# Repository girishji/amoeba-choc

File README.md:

# amoeba-choc
Single switch pcb for Kailh Choc keyboard switch (KiCad project).

If you are interested in using, here is some info:
- Use 1.2mm thickness pcb (suitable for Choc 1350 hotswap sockets)
- If you are using jlcpcb pick the option to let them panelize (5x5 will
    fit in 100x100 board ($2+shipping))
- Diodes are SOD-123 (1N4148)
- LED is SMD 6028 monochrome (you can get white ones from aliexpress). Wire
  them in a charlieplex and use IS31FL3731 LED driver (Adafruit sells a breakout
  board). 
- Some notes on LED:
    - IS31FL3731 drives (PWM) LEDs at 8k Hz. This causes audible buzz
      (annoying) from the ceramic capacitors on board of Adafruit board. To
      remove noise replace the 2 10uF capacitors with Tantalum capacitors.
      Also, you can create your own circuit for IS31FL3731 (jlcpcb stocks the
      parts) using the datasheet from Lumissil. Adafruit also has Eagle files
      on github that you can easily turn into Gerber files.
    - You can use RGB leds if you are into that. Just create two additional
      pads for soldering. You need two IS31FL3731s.
    - Do NOT use SK6812 mini-E. They are power hungry and not suitable for
      per-key LED. They are similar to sk6812 or ws2812b and they
      all have an IC inside them that does PWM. Each can draw upto 20mA. They
      draw 1mA even when turned off. You'll easily reach 500mA (or 900mA) limit
      of USB 2.0 (3.0) port. Laptop battery drains quickly. OTOH IS31FL3731
      draws 2mA (and you only need one) when LEDs are turned off and each LED get 2 or 3mA.
 - Note on soldering: You can use 'magnet wire' and eliminate the need to strip
   insulation. Get .2-.3mm single-insulation type and you can melt off the
   insulation at the tip using soldering iron and a dab of solder (there are
   some youtube videos).

  Here are some images of keyboard built using this pcb.

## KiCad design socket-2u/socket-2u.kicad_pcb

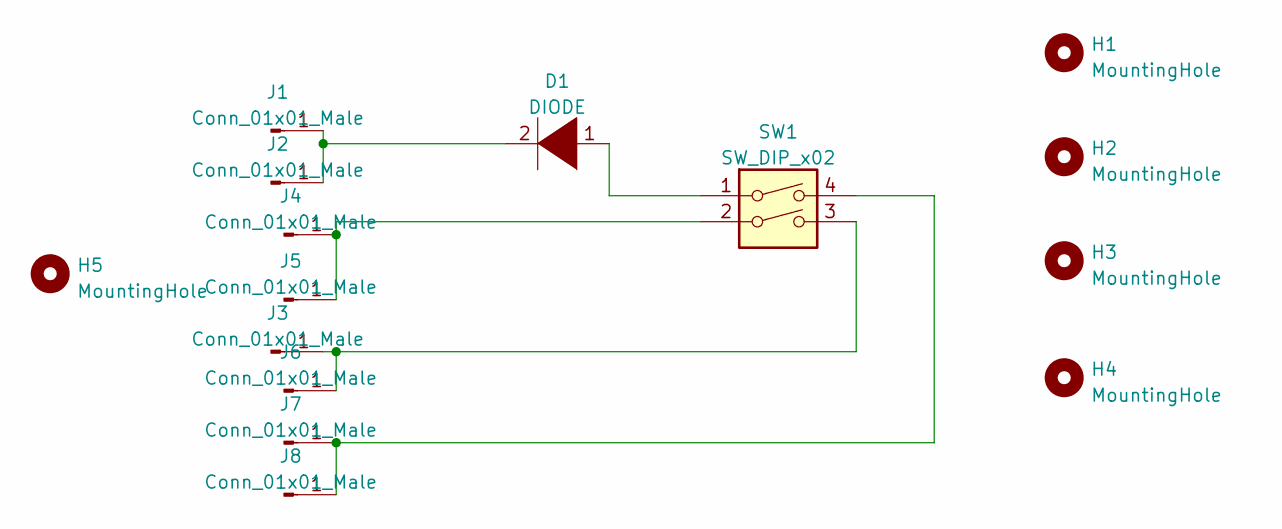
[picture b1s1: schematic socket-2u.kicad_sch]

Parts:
D1: DIODE; D_SOD-123
H1, H2, H3, H4: MountingHole; MountingHole_1.2mm_M1
H5: MountingHole; Kailh-PG1350-2u-stabilizer-refined
J1, J2, J4, J5, J6, J7, J8: Conn_01x01_Male; TestPoint_THTPad_1.0x2.5mm_Drill0.5mm
J3: Conn_01x01_Male; TestPoint_THTPad_1.0x1.5mm_Drill0.5mm
SW1: SW_DIP_x02; SW_Hotswap_Kailh_Choc_V1_plated_girish2

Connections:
unnamed: D1.1 (K), SW1.1
unnamed: D1.2 (A), J1.1, J2.1
unnamed: J3.1, J6.1, SW1.3
unnamed: J4.1, J5.1, SW1.2
unnamed: J7.1, J8.1, SW1.4

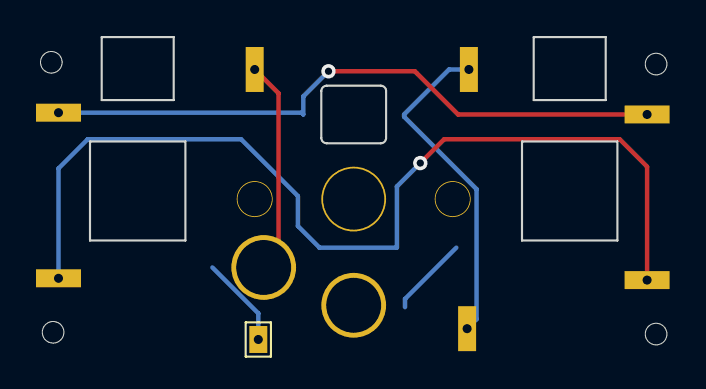
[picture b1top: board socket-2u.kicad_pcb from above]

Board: 2 copper layers, 15 parts (1 on the bottom side), 5 nets.

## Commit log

2022-03-18 Update README.md
    Type
2022-03-18 Add layout and schematic designs
    M .gitignore
    A fp-lib-table
    A kailh-choc-socket.kicad_pcb
    A kailh-choc-socket.kicad_prl
    A kailh-choc-socket.kicad_pro
    A kailh-choc-socket.kicad_sch
2022-03-23 Added LED and connector pads
    Added footprint library, LED cutout, connectors and layer details.
    M .gitignore
    A Giri-Kailh-Choc-Library.pretty/Kailh-PG1350-2u-stabilizer.kicad_mod
    A Giri-Kailh-Choc-Library.pretty/SMD_6028_White_LED.kicad_mod
    A Giri-Kailh-Choc-Library.pretty/SW_Hotswap_Kailh_Choc_V1_plated_dummy.kicad_mod
    A Giri-Kailh-Choc-Library.pretty/SW_Hotswap_Kailh_Choc_V1_plated_girish.kicad_mod
2022-03-23 Added layer details
    M .gitignore
    M README.md
    M fp-lib-table
    M kailh-choc-socket.kicad_pcb
    M kailh-choc-socket.kicad_prl
    M kailh-choc-socket.kicad_pro
2022-03-23 Add image
    M README.md
    A pcbv.png
2022-03-23 Add new footprints for mounting holes
    A Giri-Kailh-Choc-Library.pretty/D_SOD-123.kicad_mod
    A Giri-Kailh-Choc-Library.pretty/MountingHole_1.2mm_M1.kicad_mod
    D Giri-Kailh-Choc-Library.pretty/SW_Hotswap_Kailh_Choc_V1_plated_girish.kicad_mod
    M Giri-Kailh-Choc-Library.pretty/SW_Hotswap_Kailh_Choc_V1_plated_girish2.kicad_mod
    M Giri-Kailh-Choc-Library.pretty/TestPoint_THTPad_1.0x1.5mm_Drill0.5mm.kicad_mod
    A Giri-Kailh-Choc-Library.pretty/TestPoint_THTPad_1.0x2.5mm_Drill0.5mm.kicad_mod
2022-03-23 Rename kailh-choc-socket.kicad_pcb to amoeba-choc.kicad_pcb
2022-03-23 Rename kailh-choc-socket.kicad_prl to amoeba-choc.kicad_prl
2022-03-23 Rename kailh-choc-socket.kicad_pro to amoeba-choc.kicad_pro
2022-03-23 Rename kailh-choc-socket.kicad_sch to amoeba-choc.kicad_sch
2022-03-23 Renamed project files
    M .gitignore
    M amoeba-choc.kicad_pcb
    M amoeba-choc.kicad_prl
    M amoeba-choc.kicad_pro
2022-03-23 Added 2u footprint and cleanedup traces
    A Giri-Kailh-Choc-Library.pretty/Kailh-PG1350-2u-stabilizer-refined.kicad_mod
    M amoeba-choc.kicad_pcb
    M amoeba-choc.kicad_prl
    M amoeba-choc.kicad_sch
    A socket-2u/.gitignore
    A socket-2u/fp-lib-table
2022-03-23 updated image file
    M pcbv.png
2022-03-24 Update readme file
    M README.md
2022-04-30 Update readme file
    M README.md
    M amoeba-choc.kicad_prl
    M amoeba-choc.kicad_pro
2022-07-21 M .gitignore A "Giri-Kailh-Choc-Library.pretty/Adafruit IS31FL3731 Breakout.kicad_dru" A "Giri-Kailh-Choc-Library.pretty/Adafruit IS31FL3731 Breakout.kicad_pcb" A "Giri-Kailh-Choc-Library.pretty/Adaf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
